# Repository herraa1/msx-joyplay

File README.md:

# Sony Playstation controller adapter for MSX (msx-joyplay) v2

Connect [Sony PlayStation controllers](https://en.wikipedia.org/wiki/PlayStation_(console)#Controllers) to [MSX computers](https://www.msx.org/wiki/).

> [!NOTE]
>
> No build instructions are yet provided, but if you are brave enough go for the [recommended build](#recommended-build).
>

## Introduction

The msx-joyplay v2 is an adapter that allows connecting Sony PlayStation controllers to [MSX general purpose I/O ports](https://www.msx.org/wiki/General_Purpose_port).

The main features of the msx-joyplay v2 adapter are:
* small footprint
* made of widely available electronic components
* behaves as a cord extension between the MSX computer and the Sony PlayStation controller
* uses a female standard DE9 connector on the adapter's MSX joystick side
* uses a PlayStation Controller socket on the adapter's Sony PlayStation controller side
* no need for external power supply, the adapter draws current from the MSX port
* low power consumption (<20mA)
* serial debug provides information about the operation of the adapter

## [Hardware](hardware/kicad/)

The msx-joyplay v2 adapter uses an [Atmega328p](https://en.wikipedia.org/wiki/ATmega328) to convert the [Sony PlayStation SPI-like controller signalling](https://store.curiousinventor.com/guides/PS2) to the [MSX joystick standard signalling](https://www.msx.org/wiki/Joystick_control).

A two-sided printed circuit board (PCB) is used to put together all components:
* An Atmega328p as the main MCU working at +3.3V and clocked at 8MHz
* An AMS1117-3.3 regulator to convert the 5V from the joystick port to the 3.3V used for the Atmega328p chip and the PlayStation controller
* Two 74LS03 quad 2-input NAND gates with open collectors to completely mimic the standard MSX joystick behavior
* A PTC fuse to minimize damage to the MSX computer in case something goes wrong with the board
* Several additional required components (crystal, diode, leds, resistors, ceramic capacitors and a tantalum capacitor)
* An angled PSX socket is used to directly connect the Sony PlayStation controller
* A PH2.0 connector is used to connect the MSX cable extension
* A 2.54 pitch debug header is added for serial debug and programming
* An ICSP header is provided for burning a bootloader or to flash the chip using a hardware programmer

Connection to the MSX general purpose I/O port is implemented using a DE9 joystick extension cable with a female DE9 connector on one side and a loose end on the other side.
The MSX joystick extension cable loose end is wired according to the following pinout mapping.

|  |
|:--|
| MSX joystick connector pinout, from controller plug side |

| MSX side pin | Cable color (may vary) | Signal |
| ------------ | ---------------------- | ------ |
| 5            | Brown                  | +5v    |
| 4            | Orange                 | RIGHT  |
| 3            | Grey                   | LEFT   |
| 2            | Black                  | DOWN   |
| 1            | Red                    | UP     |
| 6            | Green                  | TRIGA  |
| 7            | White                  | TRIGB  |
| 8            | Blue                   | OUT    |
| 9            | Yellow                 | GND    |

The msx-joyplay-v2 is fully compatible with MSX joysticks and honors the pin8 (OUT) signal.

The adapter uses open collector outputs (using 74LS03 Quad 2-Input NAND gates with open collector outputs) which makes the adapter safer [^2] than the
standard MSX joystick schematic depicted in the MSX Technical Data Book, as it avoids a series of undesired conditions that can lead to bus contention/short circuits.

Power is drawn from the +5V signal of the MSX general purpose I/O port, which is capable of delivering up to 50mA [^1].
The msx-joyplay v2 draws below 20mA from the port when a controller is connected, so it is on the safe side. Anyway, the msx-joyplay adapter uses a Positive Temperature Coeficient (PTC) resettable fuse of 50mA (F1) to limit current in case something goes wrong.

Also on the power side, a [1N5819 Schottky diode](https://www.diodes.com/assets/Datasheets/1N5819HW.pdf) (D1) is used to avoid leaking current from the msx-joyplay adapter to the MSX in case power is applied to one of the VCC pins available on the ICSP or Debug headers while the adapter is plugged into an MSX.

Connection to the Sony PlayStation controller is done via a Sony PlayStation controller socket.

|  |
|:--|
| Sony PlayStation connector pinout, from Sony PlayStation controller side |

| PSX socket pin | Cable color official | Signal       | Comment                                                                   |
| -------------- | ---------------------| ------------ | ------------------------------------------------------------------------- |
| 1              | Brown                | DAT  / MISO  | data line, controller -> msx, open-collector signal                       |
| 2              | Orange               | CMD  / MOSI  | cmd line, msx -> controller, uses 3v3 logic                               |
| 3              | Grey                 | RUMBLE POWER | 7.6V power, not used (rumble not supported)                               |
| 4              | Black                | GND          | ground                                                                    |
| 5              | Red                  | +3V3         | +3V3 power                                                                |
| 6              | Yellow               | ATTN / SS    | select line, msx -> controller, uses 3v3 logic                            |
| 7              | Blue                 | CLK  / SCK   | clock line, msx -> controller, uses 3v3 logic                             |
| 8              | n/c                  |              |                                                                           |
| 9              | Green                | ACK          | ack line, controller -> msx, open-collector signal                        |

The Sony PlayStation controller uses 3.3V for power and logic, except for the rumble motor which uses 7.6V.

Power for the Sony PlayStation controller is provided by the 3.3V regulator on the msx-joyplay board.

### Recommended Build

Please, use [msx-joyplay-v2 Build2](#build2) for making new boards if you want something field-tested.

### [Build2](hardware/kicad/msx-joyplay-v2-build2)

[Bill Of Materials (BoM)](https://html-preview.github.io/?url=https://raw.githubusercontent.com/herraa1/msx-joyplay-v2/main/hardware/kicad/msx-joyplay-v2-build2/bom/ibom.html)

The Build2 adapter mimics completely the standard MSX joystick behaviour:

* When pin8 is HIGH, the adapter puts all stick and triggers signals in high impedance mode irrespective of their status (as if stick and triggers were not hold in the standard MSX joystick schematic), which become HIGH on the MSX side via the MSX PSG related circuitry pull-ups (matching the expected behavior)
* When pin8 is LOW
  * if a stick direction or trigger is hold, the corresponding signal is pulled down to GND causing it to be LOW (matching the expected behavior)
  * if a stick direction or trigger is not hold, the corresponding signal is put in high impedance mode, which becomes HIGH on the MSX side via the MSX PSG related circuitry pull-ups (matching the expected behaviour)

This build uses discrete logic components to honor the pin8 signaling (two [74LS03DR quad 2-input positive-nand gates with open collector outputs](https://www.ti.com/lit/ds/symlink/sn74ls03.pdf)) and uses open collector outputs which makes the adapter safer [^2] than the standard MSX joystick schematic depicted in the MSX Technical Data Book, as it avoids a series of undesired conditions that can lead to bus contention/short circuits.

## [Firmware](firmware/msx-joyplay-v2/)

The msx-joyplay v2 adapter firmware uses [SukkoPera's PsxNewLib library](https://github.com/SukkoPera/PsxNewLib) to read the Sony PlayStation controller status.

The following elements are used as inputs:
* digital pad (D-Pad), as direction arrows
* left analog pad, as direction arrows
* square button, as Trigger 1
* triangle button, as Trigger 2

Those elements' status are processed by the msx-joyplay firmware and transformed into MSX general purpose I/O port's signals on the fly.

## [Enclosure](enclosure/)

### Acrylic

A simple acrylic enclosure design for the project is provided to protect the electronic components and provide strain relief for the extension cords.

The enclosure uses a 3mm acrylic sheet.

## References

MSX general purpose I/O port
* https://www.msx.org/wiki/General_Purpose_port

PlayStation controller pinout and protocol
* https://store.curiousinventor.com/guides/PS2

Atmega328p pinout
- https://camo.githubusercontent.com/18796d8b7673e3b6c14b6bdfb61d86b58c6f0d670398973abd4207afce960277/68747470733a2f2f692e696d6775722e636f6d2f6e6177657145362e6a7067

SukkoPera PsxNewLib project
* https://github.com/SukkoPera/PsxNewLib

[^1]: https://www.msx.org/wiki/General_Purpose_port
[^2]: https://www.msx.org/wiki/Joystick/joypad_controller (see "Undesired Conditions")

## Image Sources

* https://www.oshwa.org/open-source-hardware-logo/
* https://en.wikipedia.org/wiki/File:Numbered_DE9_Diagram.svg

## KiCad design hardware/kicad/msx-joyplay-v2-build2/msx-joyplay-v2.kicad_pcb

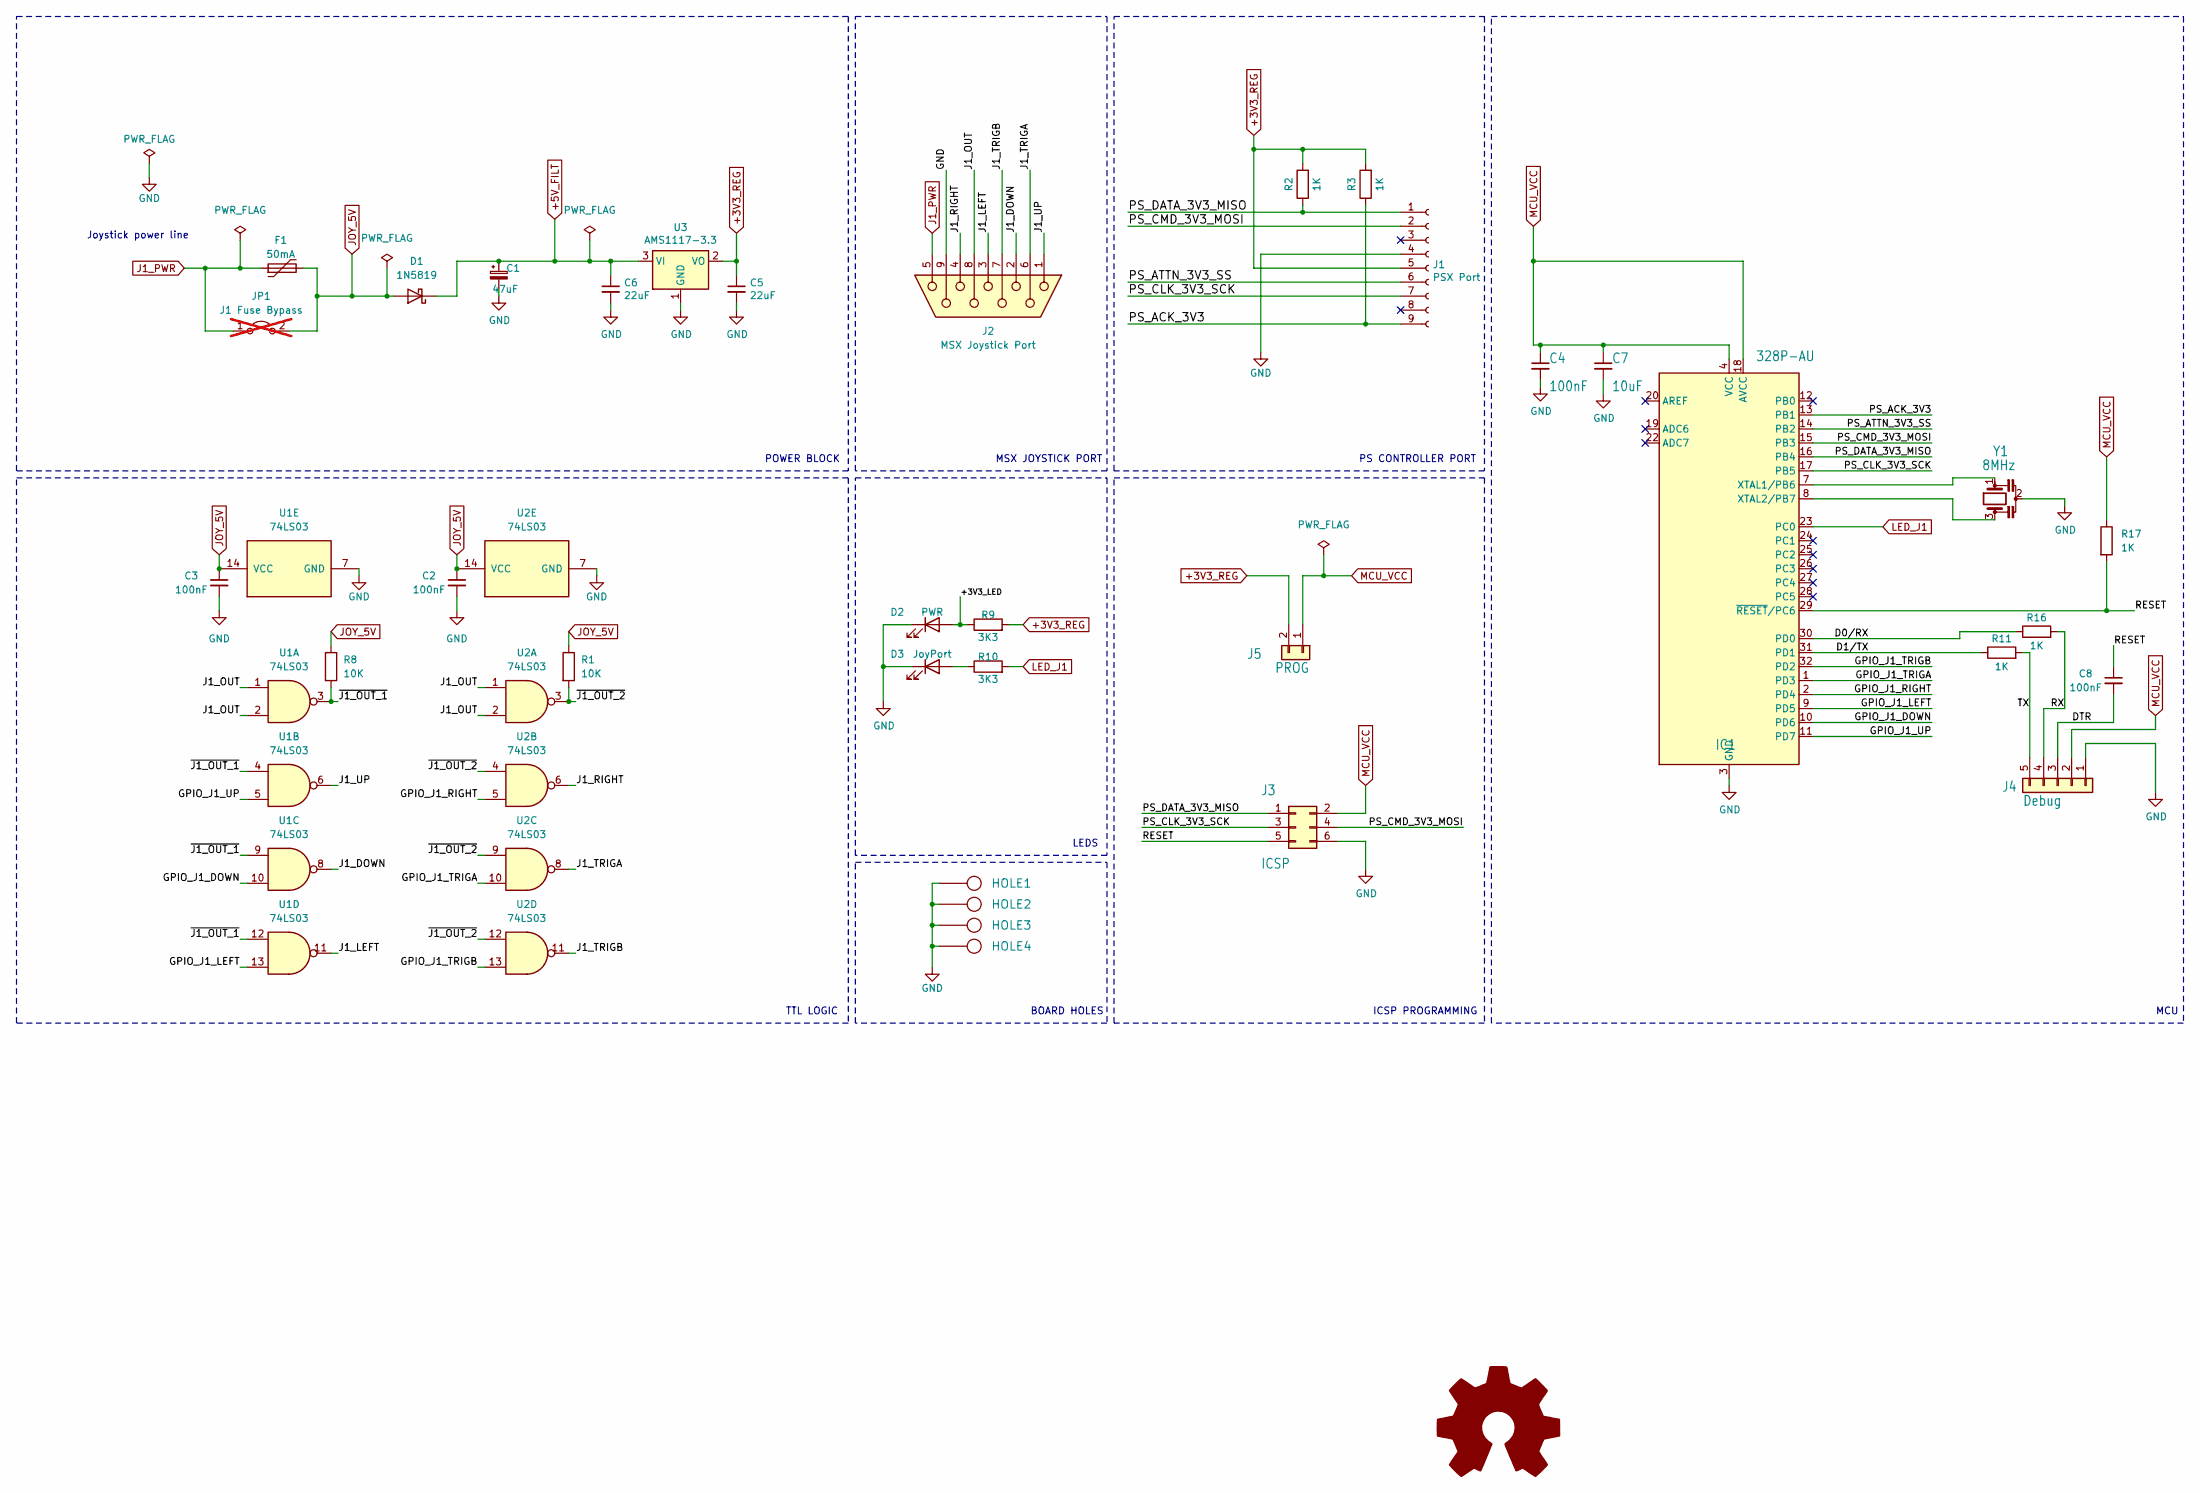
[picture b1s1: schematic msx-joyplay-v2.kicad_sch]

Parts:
C1: 47uF; CP_EIA-3216-18_Kemet-A_Pad1.58x1.35mm_HandSolder
C2, C3, C4, C8: 100nF; C_0805_2012Metric_Pad1.18x1.45mm_HandSolder
C5, C6: 22uF; C_0805_2012Metric_Pad1.18x1.45mm_HandSolder
C7: 10uF; C_0805_2012Metric_Pad1.18x1.45mm_HandSolder
D1: 1N5819; D_SOD-123
D2: PWR; LED_0805_2012Metric_Pad1.15x1.40mm_HandSolder
D3: JoyPort; LED_0805_2012Metric_Pad1.15x1.40mm_HandSolder
F1: 50mA; Fuse_1206_3216Metric_Pad1.42x1.75mm_HandSolder
HOLE1, HOLE2, HOLE3, HOLE4: HOLE; Hole_3mm
IC1: 328P-AU; TQFP-32_7x7mm_P0.8mm
J1: PSX Port; PSX_Pad_Connector
J2: MSX Joystick Port; JST_PH_B9B-PH-K_1x09_P2.00mm_Vertical
J3: ICSP; PinHeader_2x03_P2.54mm_Vertical
J4: Debug; PinHeader_1x05_P2.54mm_Vertical
J5: PROG; PinHeader_1x02_P2.54mm_Vertical
JP1: J1 Fuse Bypass; PinHeader_1x02_P2.54mm_Vertical; not fitted
R1, R8: 10K; R_0805_2012Metric_Pad1.20x1.40mm_HandSolder
R2, R3, R11, R16, R17: 1K; R_0805_2012Metric_Pad1.20x1.40mm_HandSolder
R9: 3K3; R_0805_2012Metric_Pad1.20x1.40mm_HandSolder
R10: 3K3; R_0805_2012Metric_Pad1.20x1.40mm_HandSolder; LCSC C4310
SYM1: Logo_Open_Hardware_Large; OSHW-Logo_7.5x8mm_SilkScreen
U1, U2: 74LS03; SOIC-14_3.9x8.7mm_P1.27mm
U3: AMS1117-3.3; SOT-223-3_TabPin2
Y1: 8MHz; Resonator_SMD_Murata_CSTxExxV-3Pin_3.0x1.1mm_HandSoldering

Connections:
+3V3_REG: C5.1, J1.5, J5.2, R2.2, R3.2, R9.2, U3.2 (VO)
+5V_FILT: C1.1, C6.1, D1.1 (K), U3.3 (VI)
/+3V3_LED: D2.2 (A), R9.1
/D0/RX: IC1.30 (PD0), R16.1
/D1/TX: IC1.31 (PD1), R11.1
/DTR: C8.2, J4.3
/GPIO_J1_DOWN: IC1.10 (PD6), U1.10
/GPIO_J1_LEFT: IC1.9 (PD5), U1.13
/GPIO_J1_RIGHT: IC1.2 (PD4), U2.5
/GPIO_J1_TRIGA: IC1.1 (PD3), U2.10
/GPIO_J1_TRIGB: IC1.32 (PD2), U2.13
/GPIO_J1_UP: IC1.11 (PD7), U1.5
/J1_DOWN: J2.2, U1.8
/J1_LEFT: J2.3, U1.11
/J1_OUT: J2.8, U1.1, U1.2, U2.1, U2.2
/J1_RIGHT: J2.4, U2.6
/J1_TRIGA: J2.6, U2.8
/J1_TRIGB: J2.7, U2.11
/J1_UP: J2.1, U1.6
/PS_ACK_3V3: IC1.13 (PB1), J1.9, R3.1
/PS_ATTN_3V3_SS: IC1.14 (PB2), J1.6
/PS_CLK_3V3_SCK: IC1.17 (PB5), J1.7, J3.3
/PS_CMD_3V3_MOSI: IC1.15 (PB3), J1.2, J3.4
/PS_DATA_3V3_MISO: IC1.16 (PB4), J1.1, J3.1, R2.1
/RESET: C8.1, IC1.29 (~RESET/PC6), J3.5, R17.2
/RX: J4.4, R16.2
/TX: J4.5, R11.2
/~J1_OUT_1: R8.2, U1.3, U1.4, U1.9, U1.12
/~J1_OUT_2: R1.2, U2.3, U2.4, U2.9, U2.12
GND: C1.2, C2.2, C3.2, C4.2, C5.2, C6.2, C7.2, D2.1 (K), D3.1 (K), HOLE1.1, HOLE2.1, HOLE3.1, HOLE4.1, IC1.3 (GND), IC1.5 (GND), IC1.21 (GND), J1.4, J2.9, J3.6, J4.1, U1.7 (GND), U2.7 (GND), U3.1 (GND), Y1.2
J1_PWR: F1.1, J2.5, JP1.1 (A)
JOY_5V: C2.1, C3.1, D1.2 (A), F1.2, JP1.2 (B), R1.1, R8.1, U1.14 (VCC), U2.14 (VCC)
LED_J1: IC1.23 (PC0), R10.2
MCU_VCC: C4.1, C7.1, IC1.4 (VCC), IC1.6 (VCC), IC1.18 (AVCC), J3.2, J4.2, J5.1, R17.1
unnamed: D3.2 (A), R10.1
unnamed: IC1.7 (XTAL1/PB6), Y1.1
unnamed: IC1.8 (XTAL2/PB7), Y1.3

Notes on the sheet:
MCU
LEDS
MSX JOYSTICK PORT
TTL LOGIC
BOARD HOLES
Joystick power line
ICSP PROGRAMMING
PS CONTROLLER PORT
POWER BLOCK

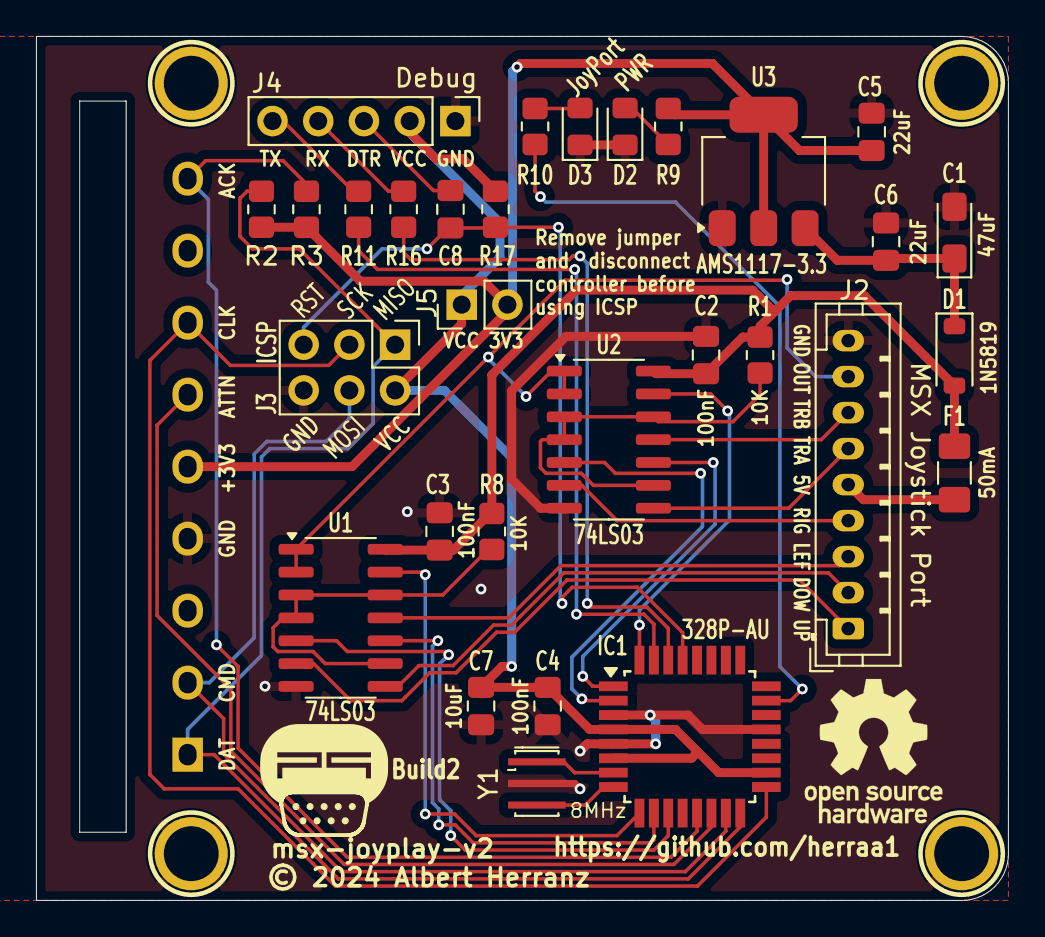
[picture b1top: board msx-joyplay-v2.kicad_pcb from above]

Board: 2 copper layers, 54.0 x 48.0 mm, 36 parts (0 on the bottom side), 37 nets.

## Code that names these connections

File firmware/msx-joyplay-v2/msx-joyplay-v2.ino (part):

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#define PSX_AXIS_MAX 255

/* MSX general purpose signals as mapped to Arduino Nano PORTD bits */
const int PORT_MSX_JOYSTICK_UP = 7;       /* PD7, MSX joystick pin1 */
const int PORT_MSX_JOYSTICK_DOWN = 6;     /* PD6, MSX joystick pin2 */
const int PORT_MSX_JOYSTICK_LEFT = 5;     /* PD5, MSX joystick pin3 */
const int PORT_MSX_JOYSTICK_RIGHT = 4;    /* PD4, MSX joystick pin4 */
const int PORT_MSX_JOYSTICK_TRIGGER1 = 3; /* PD3, MSX joystick pin6 */
const int PORT_MSX_JOYSTICK_TRIGGER2 = 2; /* PD2, MSX joystick pin7 */

volatile uint8_t curr_msx_joystick_signals = 0x00;

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
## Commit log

2024-07-08 readme: small fix, add picture with acrylic enclosure
2024-12-25 readme: add microprocessor voltage and clock
2024-12-25 readme: mention SPI as the controller protocol
2024-12-25 readme: no build instructions yet

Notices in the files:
firmware/msx-joyplay-v2/msx-joyplay-v2.ino:
Copyright (C) 2024 Albert Herranz
This code is released under GPL V2.0
Valid-License-Identifier: GPL-2.0-only
SPDX-URL: https://spdx.org/licenses/GPL-2.0-only.html
Copyright (C) 2019-2020 by SukkoPera <software@sukkology.net>
modify it under the terms of the GNU General Public License as published by
the Free Software Foundation, either version 3 of the License, or
(at your option) any later version.
hardware/kicad/msx-joyplay-v2-build2/msx-joyplay-v2.kicad_pcb:
© 2024 Albert Herranz
